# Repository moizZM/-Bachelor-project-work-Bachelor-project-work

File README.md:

# Bachelor project work
In progress. Building a small lab safety system. Sensor nodes (Raspberry Pi Pico W) send JSON over TCP to a Python server on my Linux VM. The server checks simple rules and sends commands back (flash LED, fan/beacon, safe power-off via contactor + E-STOP). Messages are newline-JSON for easy parsing.

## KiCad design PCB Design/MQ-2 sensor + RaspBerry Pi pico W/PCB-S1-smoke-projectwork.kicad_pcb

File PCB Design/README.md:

Two-layer PCB and schematic for interfacing an MQ-2 smoke sensor with Raspberry Pi Pico W. Includes fused 5 V VSYS input, potentiometer for sensitivity, LM393 comparator, and resistor divider scaling the analog signal to 3.3 V ADC (GP26). A red LED with series resistor indicates smoke detection via DOUT. Board features plated mounting holes, test points, solid ground pour, and clear silkscreen labeling for reliable operation.

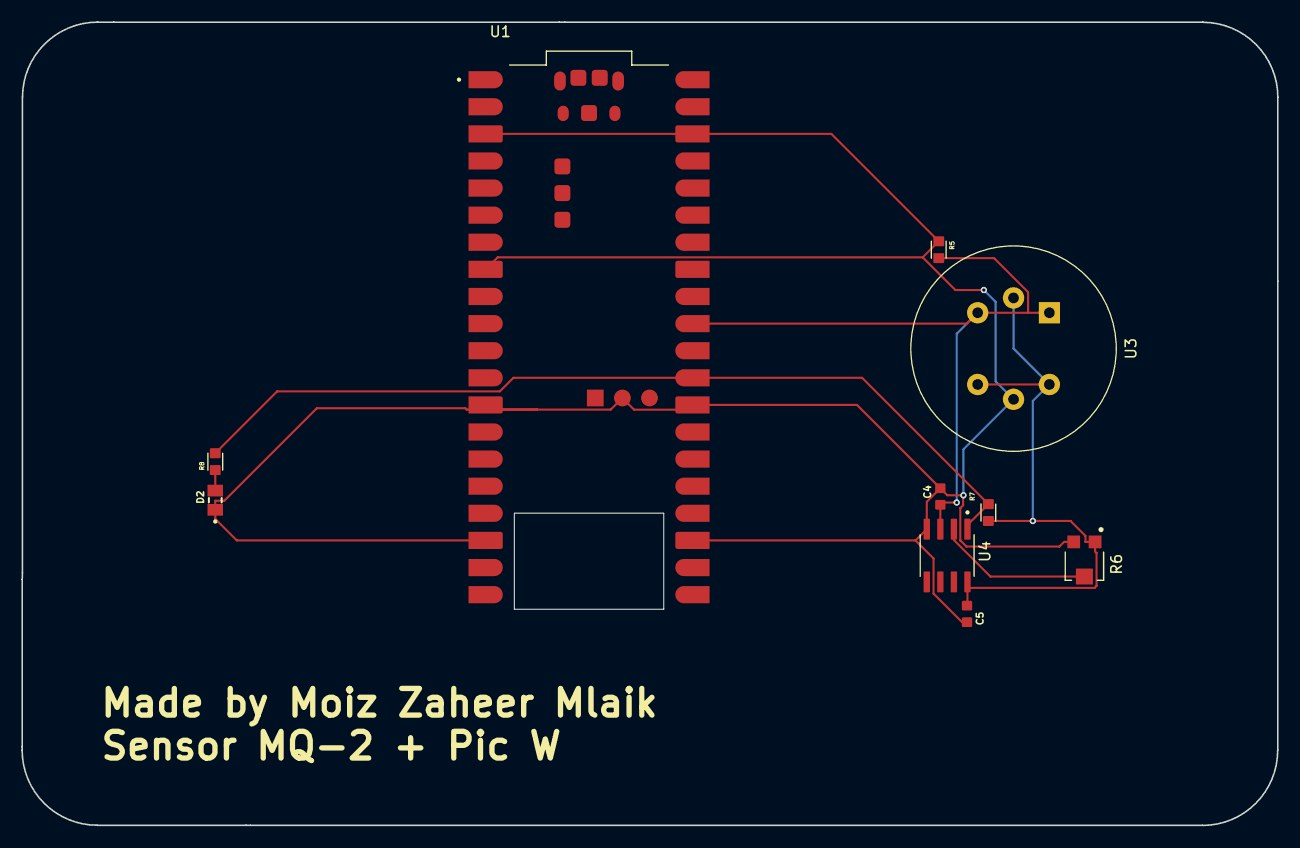
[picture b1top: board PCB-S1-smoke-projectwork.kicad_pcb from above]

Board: 2 copper layers, 117.7 x 75.3 mm, 10 parts (0 on the bottom side), 6 nets.

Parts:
C4, C5: 100n; CAPC1608X90N
D2: 597-3305-607F; LEDC2012X70N
R5, R7: 10K; RESC1608X50N
R6: TC33X-2-103E; TRIM_TC33X-2-103E
R8: 2k2; RESC1608X50N
U1: RASPBERRY_PI_PICO_W; MODULE_RASPBERRY_PI_PICO_W
U3: MQ-6
U4: LM393M_NOPB; SOIC127P599X175-8N

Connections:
+5V: C5.1, R6.1, R7.1, U3.2 (VH+), U3.4 (A2), U3.6 (A1), U4.8
/MQ-X/AOUT: C4.1, R5.2, U1.31 (I2C1_SDA/ADC0/GP26), U3.1 (B1), U3.3 (B2), U4.3
/MQ-X/DOUT: R7.2, R8.2, U1.29 (GP22), U4.1
GND: C4.2, C5.2, D2.C, R5.1, R6.3, U1.3 (GND), U1.8 (GND), U1.13 (GND), U1.18 (GND), U1.23 (GND), U1.28 (GND), U1.38 (GND), U1.F (GND), U3.5 (VH-), U4.4
unnamed: D2.A, R8.1
POT: R6.2, U4.2
